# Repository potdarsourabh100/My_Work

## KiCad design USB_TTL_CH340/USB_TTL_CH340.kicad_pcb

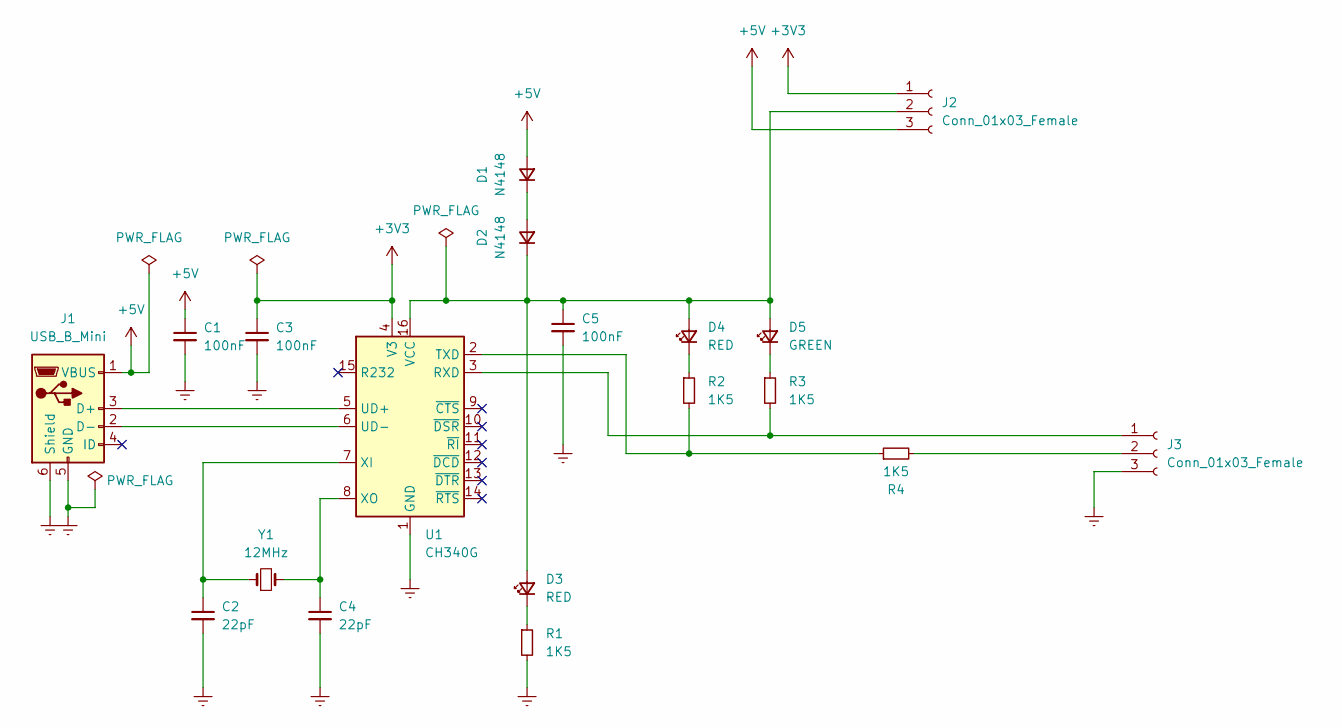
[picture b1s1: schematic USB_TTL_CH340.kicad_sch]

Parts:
C1, C3, C5: 100nF; C_1206_3216Metric_Pad1.33x1.80mm_HandSolder
C2, C4: 22pF; C_1206_3216Metric_Pad1.33x1.80mm_HandSolder
D1, D2: N4148; D_1206_3216Metric_Pad1.42x1.75mm_HandSolder
D3, D4: RED; LED_1206_3216Metric_Pad1.42x1.75mm_HandSolder
D5: GREEN; LED_1206_3216Metric_Pad1.42x1.75mm_HandSolder
J1: USB_B_Mini; USB_Micro-B_Molex-105017-0001
J2, J3: Conn_01x03_Female; PinHeader_1x03_P2.54mm_Vertical
R1, R2, R3, R4: 1K5; R_1206_3216Metric_Pad1.30x1.75mm_HandSolder
U1: CH340G; SOIC-16_3.9x9.9mm_P1.27mm
Y1: 12MHz; Crystal_HC49-U_Vertical

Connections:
+3V3: C3.1, J2.1, U1.4 (V3)
+5V: C1.1, D1.2 (A), J1.1 (VBUS), J2.3
Earth: C1.2, C2.2, C3.2, C4.2, C5.2, J1.5 (GND), J1.6 (Shield), J3.3, R1.2, U1.1 (GND)
unnamed: C2.1, U1.7 (XI), Y1.1
unnamed: C4.1, U1.8 (XO), Y1.2
unnamed: C5.1, D2.1 (K), D3.2 (A), D4.2 (A), D5.2 (A), J2.2, U1.16 (VCC)
unnamed: D1.1 (K), D2.2 (A)
unnamed: D3.1 (K), R1.1
unnamed: D4.1 (K), R2.1
unnamed: D5.1 (K), R3.1
unnamed: J1.2 (D-), U1.6 (UD-)
unnamed: J1.3 (D+), U1.5 (UD+)
unnamed: J3.1, R3.2, U1.3 (RXD)
unnamed: J3.2, R4.2
unnamed: R2.2, R4.1, U1.2 (TXD)

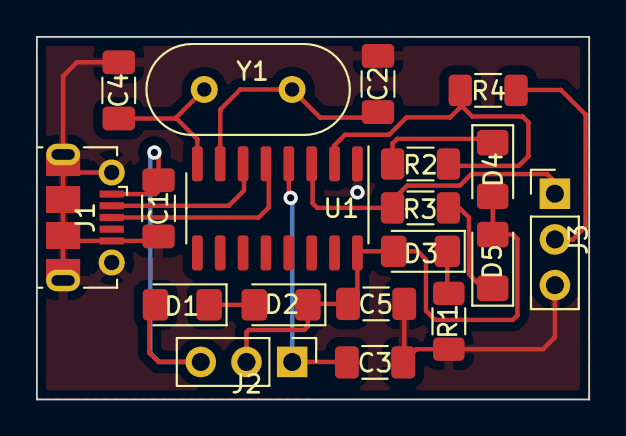
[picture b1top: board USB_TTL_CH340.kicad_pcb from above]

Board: 2 copper layers, 30.7 x 20.1 mm, 19 parts (0 on the bottom side), 15 nets.

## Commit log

2022-08-17 File Template addition
2022-08-17 File Template added
2022-08-17 File Addition for new requirments
2022-08-17 New File
2022-08-17 Folder Templates addition
2022-08-17 Battery Life Cycle tester file uploads
2022-08-26 hgchkckhg
